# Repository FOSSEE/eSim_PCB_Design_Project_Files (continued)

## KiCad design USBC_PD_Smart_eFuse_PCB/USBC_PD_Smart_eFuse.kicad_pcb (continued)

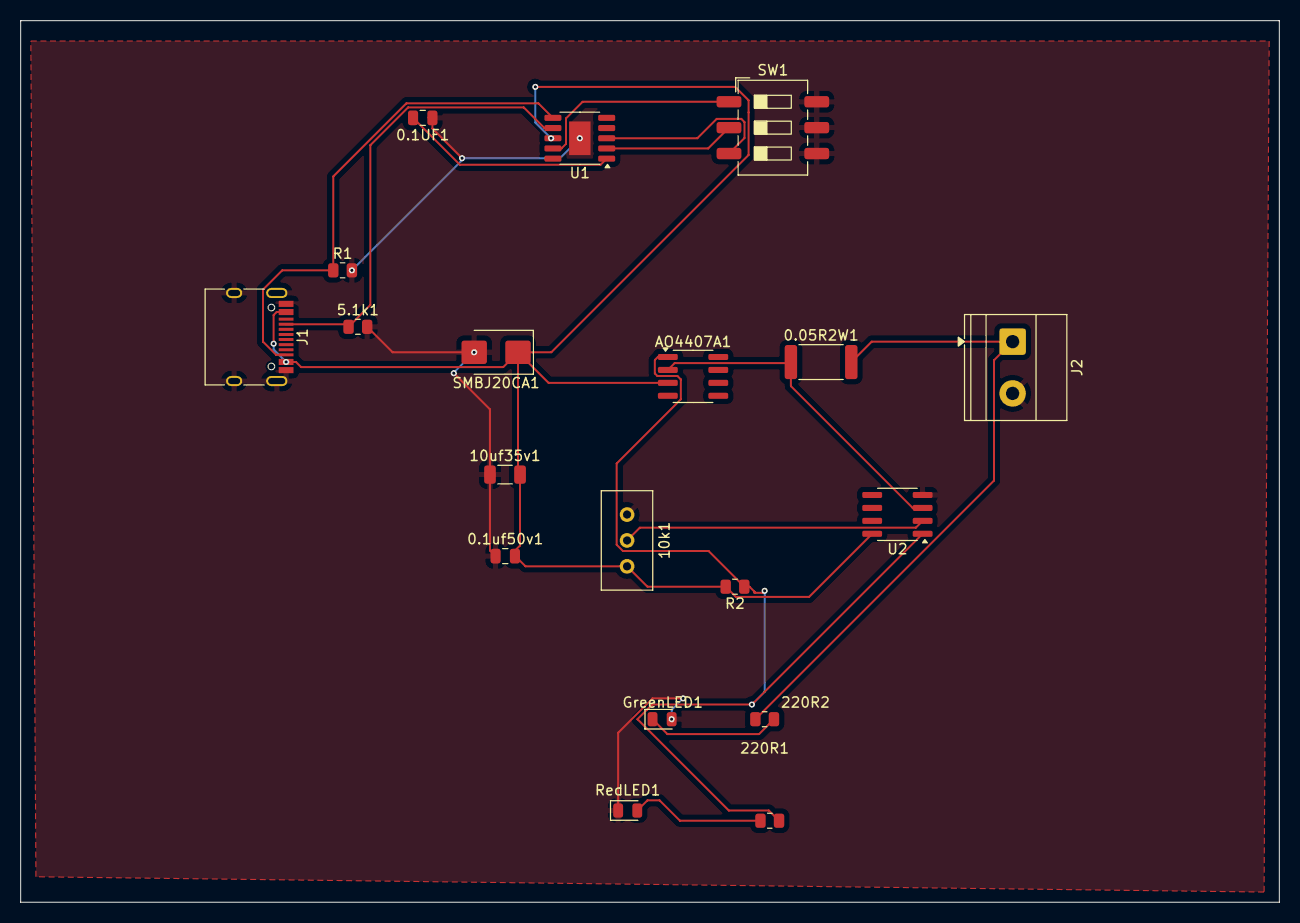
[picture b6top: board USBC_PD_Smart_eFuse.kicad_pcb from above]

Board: 4 copper layers, 123.5 x 86.5 mm, 19 parts (0 on the bottom side), 14 nets.

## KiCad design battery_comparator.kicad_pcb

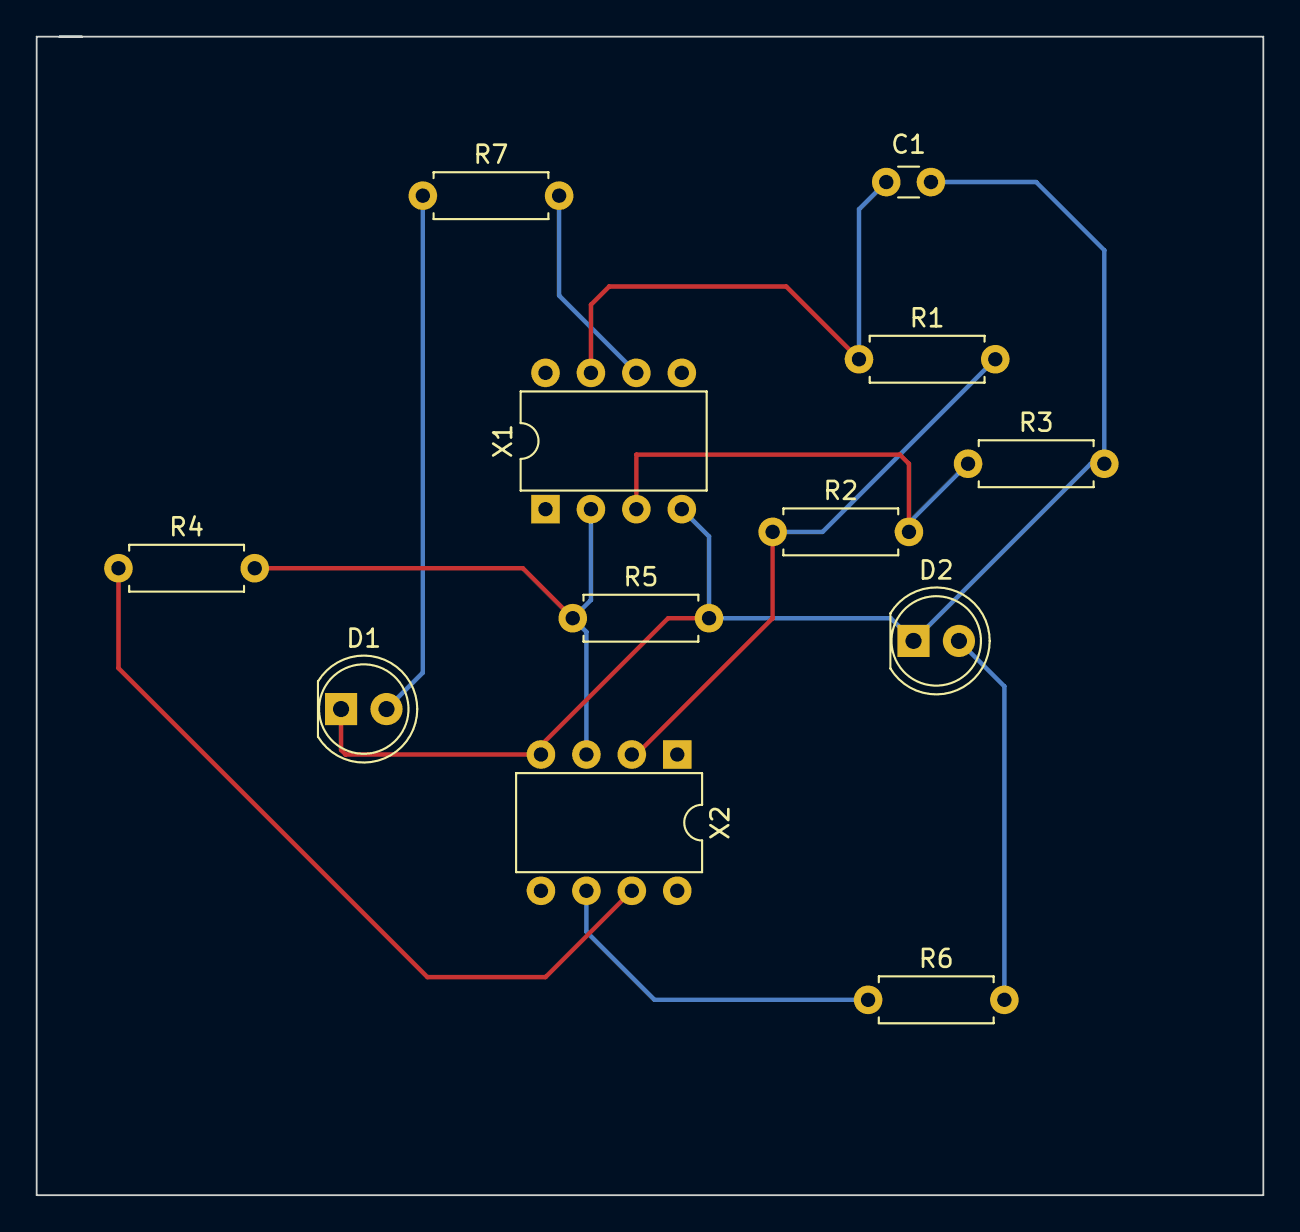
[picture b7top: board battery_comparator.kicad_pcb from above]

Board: 2 copper layers, 68.6 x 64.8 mm, 12 parts (0 on the bottom side), 10 nets.

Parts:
C1: 100n; C_Disc_D3.0mm_W1.6mm_P2.50mm
D1, D2: eSim_LED; LED_D5.0mm
R1: 4.7k; R_Axial_DIN0207_L6.3mm_D2.5mm_P7.62mm_Horizontal
R2: 3.3k; R_Axial_DIN0207_L6.3mm_D2.5mm_P7.62mm_Horizontal
R3: 2.2k; R_Axial_DIN0207_L6.3mm_D2.5mm_P7.62mm_Horizontal
R4, R5: 10k; R_Axial_DIN0207_L6.3mm_D2.5mm_P7.62mm_Horizontal
R6, R7: 330; R_Axial_DIN0207_L6.3mm_D2.5mm_P7.62mm_Horizontal
X1, X2: lm_741; DIP-8_W7.62mm

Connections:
GND: C1.2, D1.1, D2.1, R3.2, R5.2, X1.4, X2.4
unnamed: C1.1, R1.1, X1.7
unnamed: D1.2, R7.1
unnamed: D2.2, R6.2
unnamed: R1.2, R2.1, X2.2
unnamed: R2.2, R3.1, X1.3
unnamed: R4.1, X2.7
unnamed: R4.2, R5.1, X1.2, X2.3
unnamed: R6.1, X2.6
unnamed: R7.2, X1.6

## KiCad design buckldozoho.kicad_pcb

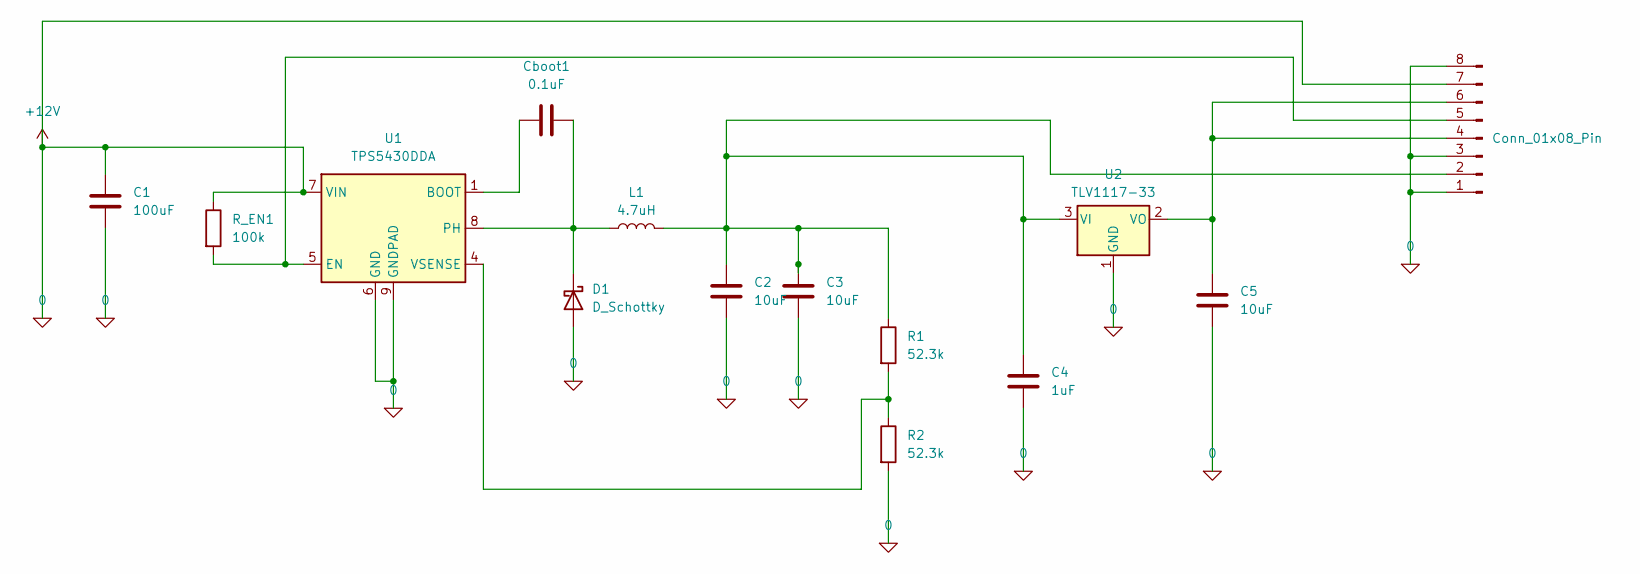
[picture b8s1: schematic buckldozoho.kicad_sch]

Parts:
C1: 100uF; C_1210_3225Metric
C2, C3, C5: 10uF; C_0805_2012Metric
C4: 1uF; C_0603_1608Metric
Cboot1: 0.1uF; C_0402_1005Metric
D1: D_Schottky; D_SMA
J1: Conn_01x08_Pin; PinHeader_1x08_P2.54mm_Horizontal
L1: 4.7uH; L_Bourns_SRR1260
R1, R2: 52.3k; R_0402_1005Metric
R_EN1: 100k; R_0402_1005Metric
U1: TPS5430DDA; TI_SO-PowerPAD-8_ThermalVias
U2: TLV1117-33; SOT-223-3_TabPin2

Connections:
+12V: C1.1, C1.2, C2.2, C3.2, C4.2, C5.2, D1.2 (A), J1.1, J1.3, J1.7, J1.8, R2.2, R_EN1.1, U1.6 (GND), U1.7 (VIN), U1.9 (GNDPAD), U2.1 (GND)
unnamed: Cboot1.2, D1.1 (K), L1.1, U1.8 (PH)
unnamed: C2.1, C3.1, C4.1, J1.2, L1.2, R1.1, U2.3 (VI)
unnamed: C5.1, J1.4, J1.6, U2.2 (VO)
unnamed: J1.5, R_EN1.2, U1.5 (EN)
unnamed: Cboot1.1, U1.1 (BOOT)
unnamed: R1.2, R2.1, U1.4 (VSENSE)

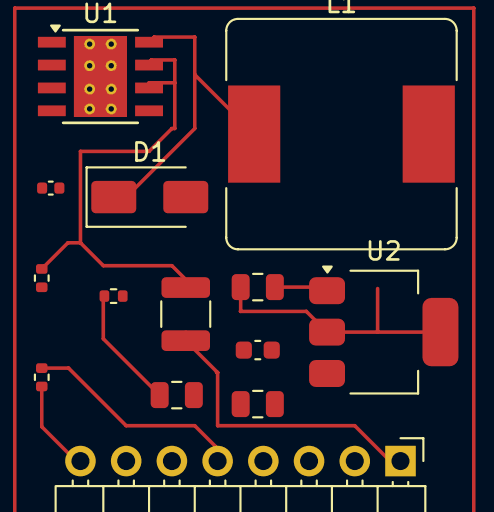
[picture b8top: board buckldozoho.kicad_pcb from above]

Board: 2 copper layers, 14 parts (0 on the bottom side), 7 nets.
